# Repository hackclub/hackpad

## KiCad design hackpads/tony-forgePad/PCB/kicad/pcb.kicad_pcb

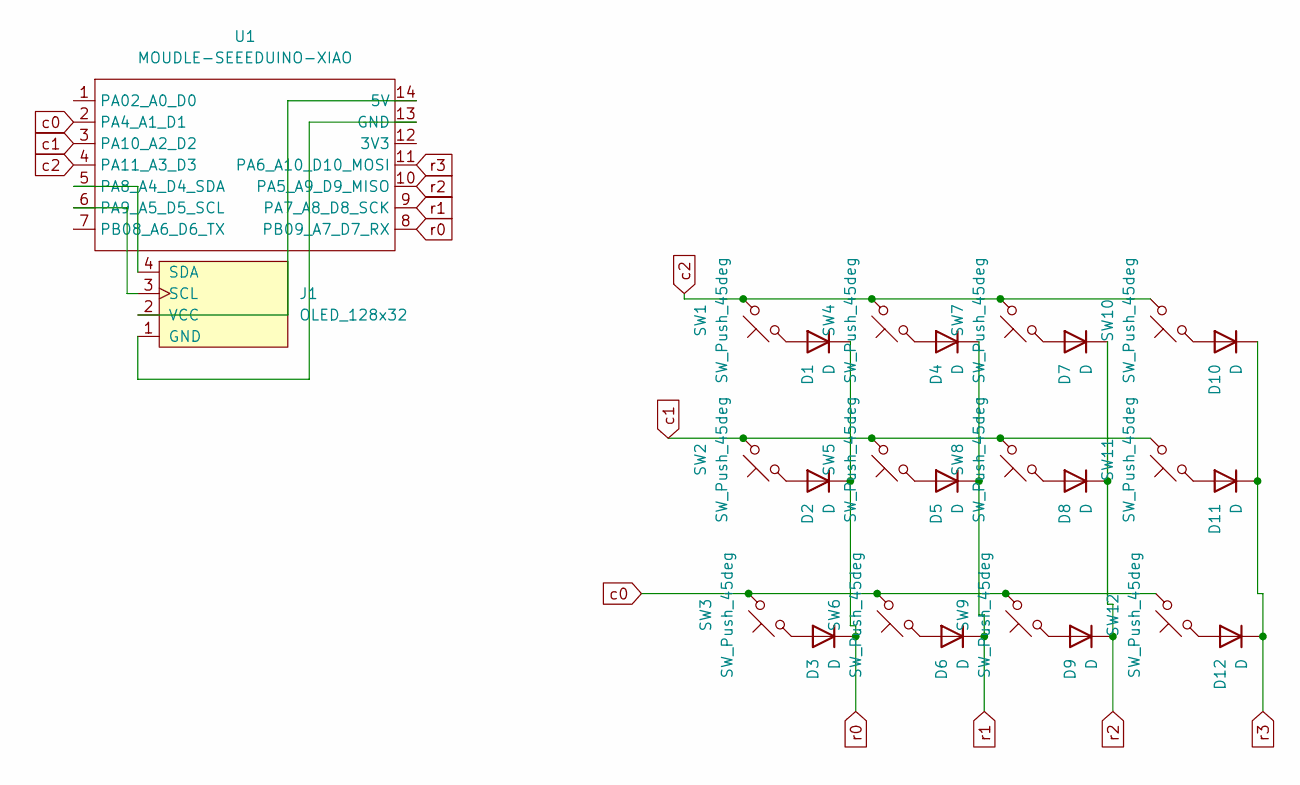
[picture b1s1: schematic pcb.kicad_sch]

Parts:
D1, D2, D3, D4, D5, D6, D7, D8, D9, D10, D11, D12: D; Diode_DO-35
J1: OLED_128x32
SW1, SW2, SW3, SW4, SW5, SW6, SW7, SW8, SW9, SW10, SW11, SW12: SW_Push_45deg; SW_Cherry_MX_1.00u_PCB
U1: MOUDLE-SEEEDUINO-XIAO; XIAO-Generic-Hybrid-14P-2.54-21X17.8MM

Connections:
unnamed: D1.2 (A), SW1.2
unnamed: D2.2 (A), SW2.2
unnamed: D3.2 (A), SW3.2
unnamed: D4.2 (A), SW4.2
unnamed: D5.2 (A), SW5.2
unnamed: D6.2 (A), SW6.2
unnamed: D7.2 (A), SW7.2
unnamed: D8.2 (A), SW8.2
unnamed: D9.2 (A), SW9.2
unnamed: D10.2 (A), SW10.2
unnamed: D11.2 (A), SW11.2
unnamed: D12.2 (A), SW12.2
unnamed: J1.1 (GND), U1.13 (GND)
unnamed: J1.3 (SCL), U1.6 (PA9_A5_D5_SCL)
unnamed: J1.4 (SDA), U1.5 (PA8_A4_D4_SDA)
unnamed: J1.2 (VCC), U1.14 (5V)
c0: SW3.1, SW6.1, SW9.1, SW12.1, U1.2 (PA4_A1_D1)
c1: SW2.1, SW5.1, SW8.1, SW11.1, U1.3 (PA10_A2_D2)
c2: SW1.1, SW4.1, SW7.1, SW10.1, U1.4 (PA11_A3_D3)
r0: D1.1 (K), D2.1 (K), D3.1 (K), U1.8 (PB09_A7_D7_RX)
r1: D4.1 (K), D5.1 (K), D6.1 (K), U1.9 (PA7_A8_D8_SCK)
r2: D7.1 (K), D8.1 (K), D9.1 (K), U1.10 (PA5_A9_D9_MISO)
r3: D10.1 (K), D11.1 (K), D12.1 (K), U1.11 (PA6_A10_D10_MOSI)

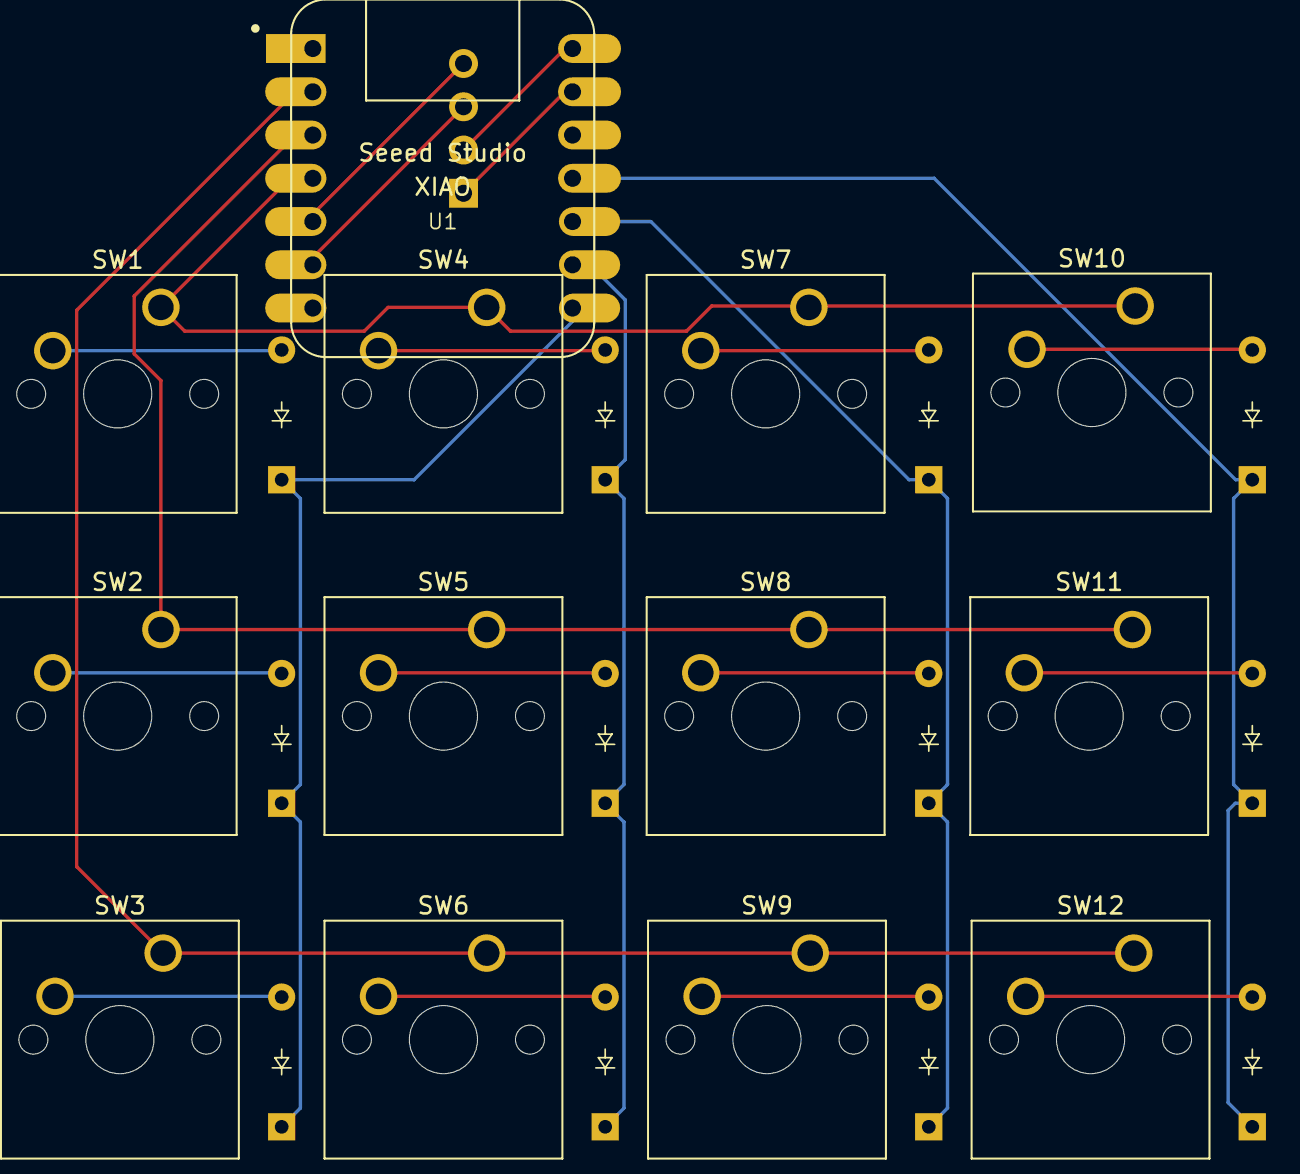
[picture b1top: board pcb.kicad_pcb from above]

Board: 2 copper layers, 26 parts (0 on the bottom side), 23 nets.

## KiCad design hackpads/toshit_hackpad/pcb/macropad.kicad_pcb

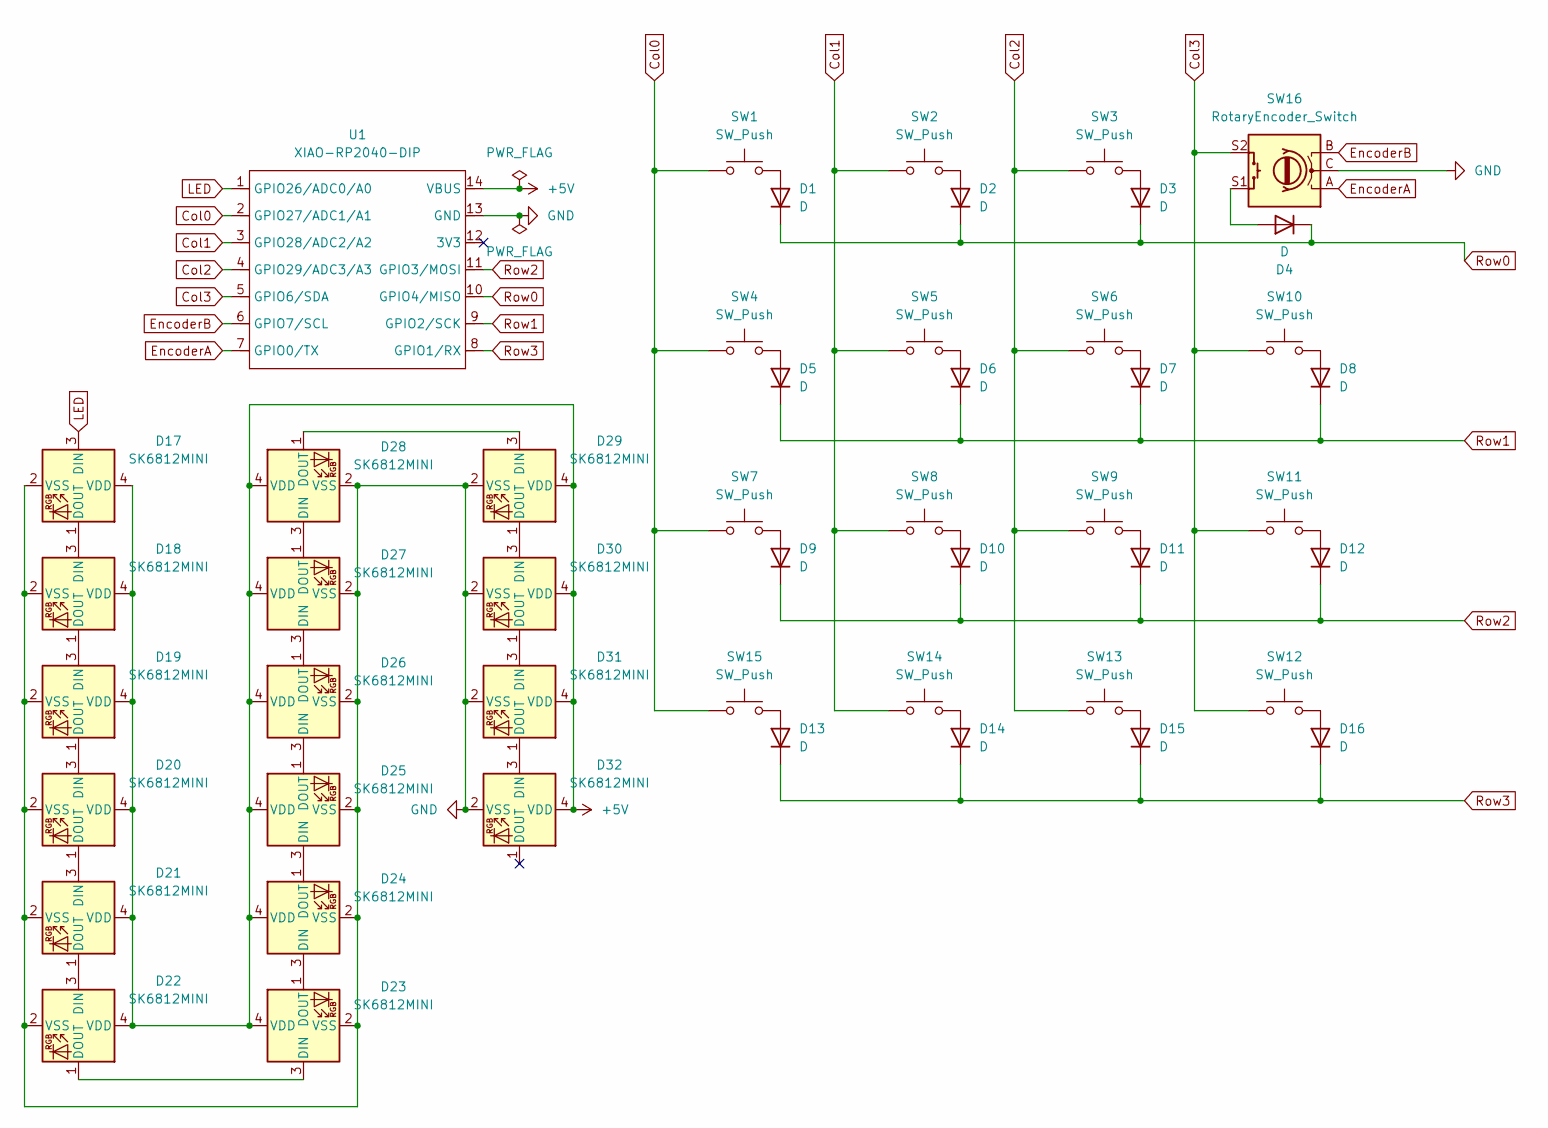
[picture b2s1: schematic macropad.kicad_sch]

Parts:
D1, D2, D3, D4, D5, D6, D7, D8, D9, D10, D11, D12, D13, D14, D15, D16: D; DIODE-1N4148
D17, D18, D19, D20, D21, D22, D23, D24, D25, D26, D27, D28, D29, D30, D31, D32: SK6812MINI; LED_SK6812MINI_PLCC4_3.5x3.5mm_P1.75mm
SW1, SW2, SW3, SW4, SW5, SW6, SW7, SW8, SW9, SW10, SW11, SW12, SW13, SW14, SW15: SW_Push; SW_Cherry_MX_1.00u_PCB
SW16: RotaryEncoder_Switch; RotaryEncoder_Alps_EC11E-Switch_Vertical_H20mm
U1: XIAO-RP2040-DIP

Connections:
+5V: D17.4 (VDD), D18.4 (VDD), D19.4 (VDD), D20.4 (VDD), D21.4 (VDD), D22.4 (VDD), D23.4 (VDD), D24.4 (VDD), D25.4 (VDD), D26.4 (VDD), D27.4 (VDD), D28.4 (VDD), D29.4 (VDD), D30.4 (VDD), D31.4 (VDD), D32.4 (VDD), U1.14 (VBUS)
Col0: SW1.1, SW4.1, SW7.1, SW15.1, U1.2 (GPIO27/ADC1/A1)
Col1: SW2.1, SW5.1, SW8.1, SW14.1, U1.3 (GPIO28/ADC2/A2)
Col2: SW3.1, SW6.1, SW9.1, SW13.1, U1.4 (GPIO29/ADC3/A3)
Col3: SW10.1, SW11.1, SW12.1, SW16.S2, U1.5 (GPIO6/SDA)
EncoderA: SW16.A, U1.7 (GPIO0/TX)
EncoderB: SW16.B, U1.6 (GPIO7/SCL)
GND: D17.2 (VSS), D18.2 (VSS), D19.2 (VSS), D20.2 (VSS), D21.2 (VSS), D22.2 (VSS), D23.2 (VSS), D24.2 (VSS), D25.2 (VSS), D26.2 (VSS), D27.2 (VSS), D28.2 (VSS), D29.2 (VSS), D30.2 (VSS), D31.2 (VSS), D32.2 (VSS), SW16.C, U1.13 (GND)
LED: D17.3 (DIN), U1.1 (GPIO26/ADC0/A0)
unnamed: D1.2 (A), SW1.2
unnamed: D2.2 (A), SW2.2
unnamed: D3.2 (A), SW3.2
unnamed: D4.2 (A), SW16.S1
unnamed: D5.2 (A), SW4.2
unnamed: D6.2 (A), SW5.2
unnamed: D7.2 (A), SW6.2
unnamed: D8.2 (A), SW10.2
unnamed: D9.2 (A), SW7.2
unnamed: D10.2 (A), SW8.2
unnamed: D11.2 (A), SW9.2
unnamed: D12.2 (A), SW11.2
unnamed: D13.2 (A), SW15.2
unnamed: D14.2 (A), SW14.2
unnamed: D15.2 (A), SW13.2
unnamed: D16.2 (A), SW12.2
unnamed: D17.1 (DOUT), D18.3 (DIN)
unnamed: D18.1 (DOUT), D19.3 (DIN)
unnamed: D19.1 (DOUT), D20.3 (DIN)
unnamed: D20.1 (DOUT), D21.3 (DIN)
unnamed: D21.1 (DOUT), D22.3 (DIN)
unnamed: D22.1 (DOUT), D23.3 (DIN)
unnamed: D23.1 (DOUT), D24.3 (DIN)
unnamed: D24.1 (DOUT), D25.3 (DIN)
unnamed: D25.1 (DOUT), D26.3 (DIN)
unnamed: D26.1 (DOUT), D27.3 (DIN)
unnamed: D27.1 (DOUT), D28.3 (DIN)
unnamed: D28.1 (DOUT), D29.3 (DIN)
unnamed: D29.1 (DOUT), D30.3 (DIN)
unnamed: D30.1 (DOUT), D31.3 (DIN)
unnamed: D31.1 (DOUT), D32.3 (DIN)
Row0: D1.1 (K), D2.1 (K), D3.1 (K), D4.1 (K), U1.10 (GPIO4/MISO)
Row1: D5.1 (K), D6.1 (K), D7.1 (K), D8.1 (K), U1.9 (GPIO2/SCK)
Row2: D9.1 (K), D10.1 (K), D11.1 (K), D12.1 (K), U1.11 (GPIO3/MOSI)
Row3: D13.1 (K), D14.1 (K), D15.1 (K), D16.1 (K), U1.8 (GPIO1/RX)

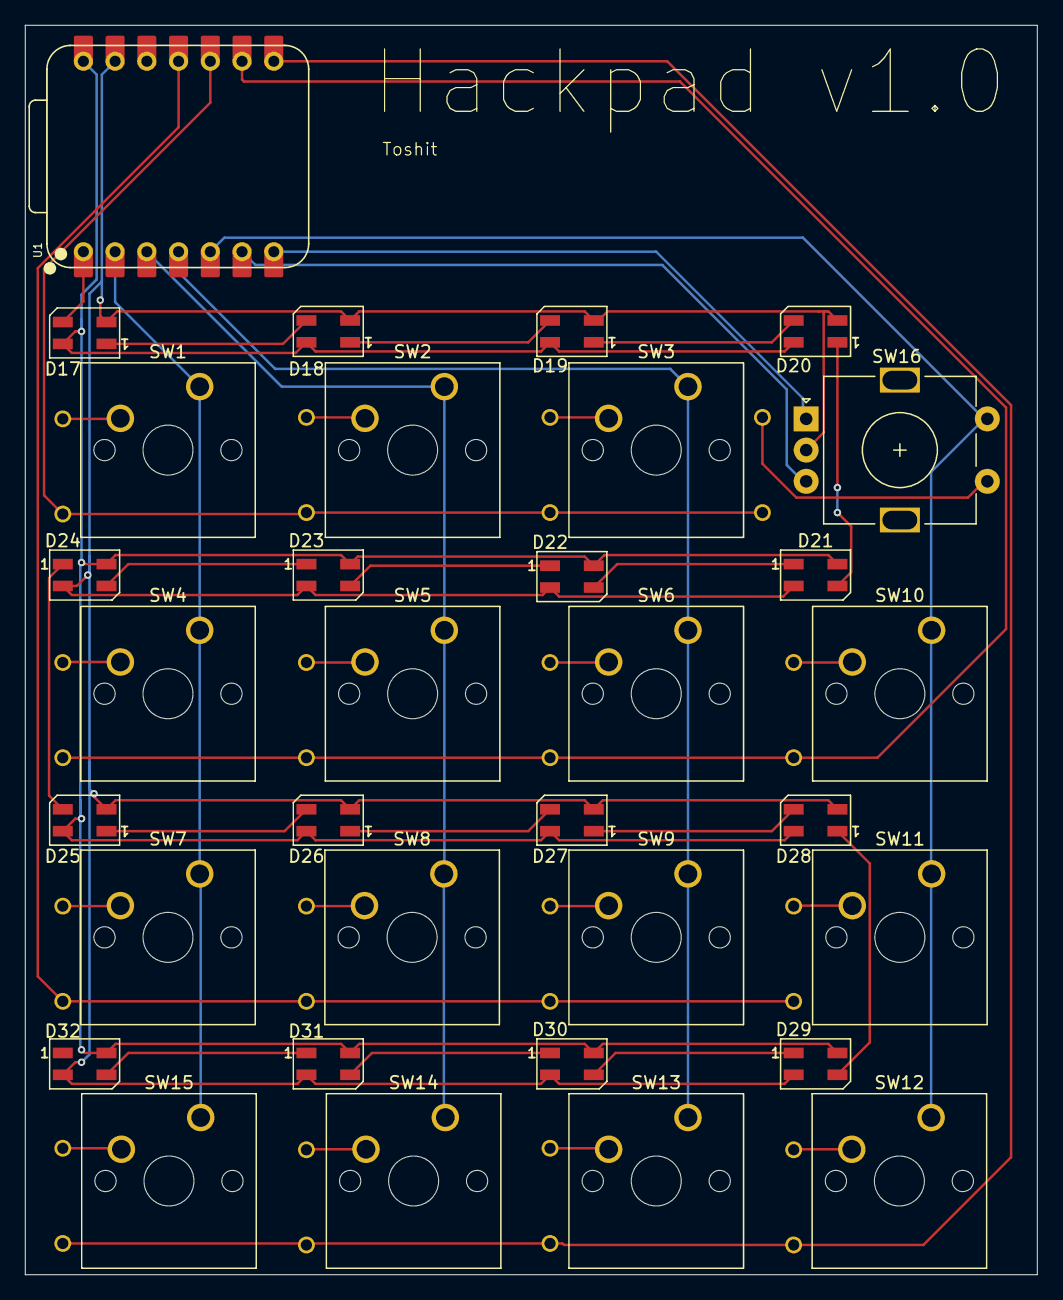
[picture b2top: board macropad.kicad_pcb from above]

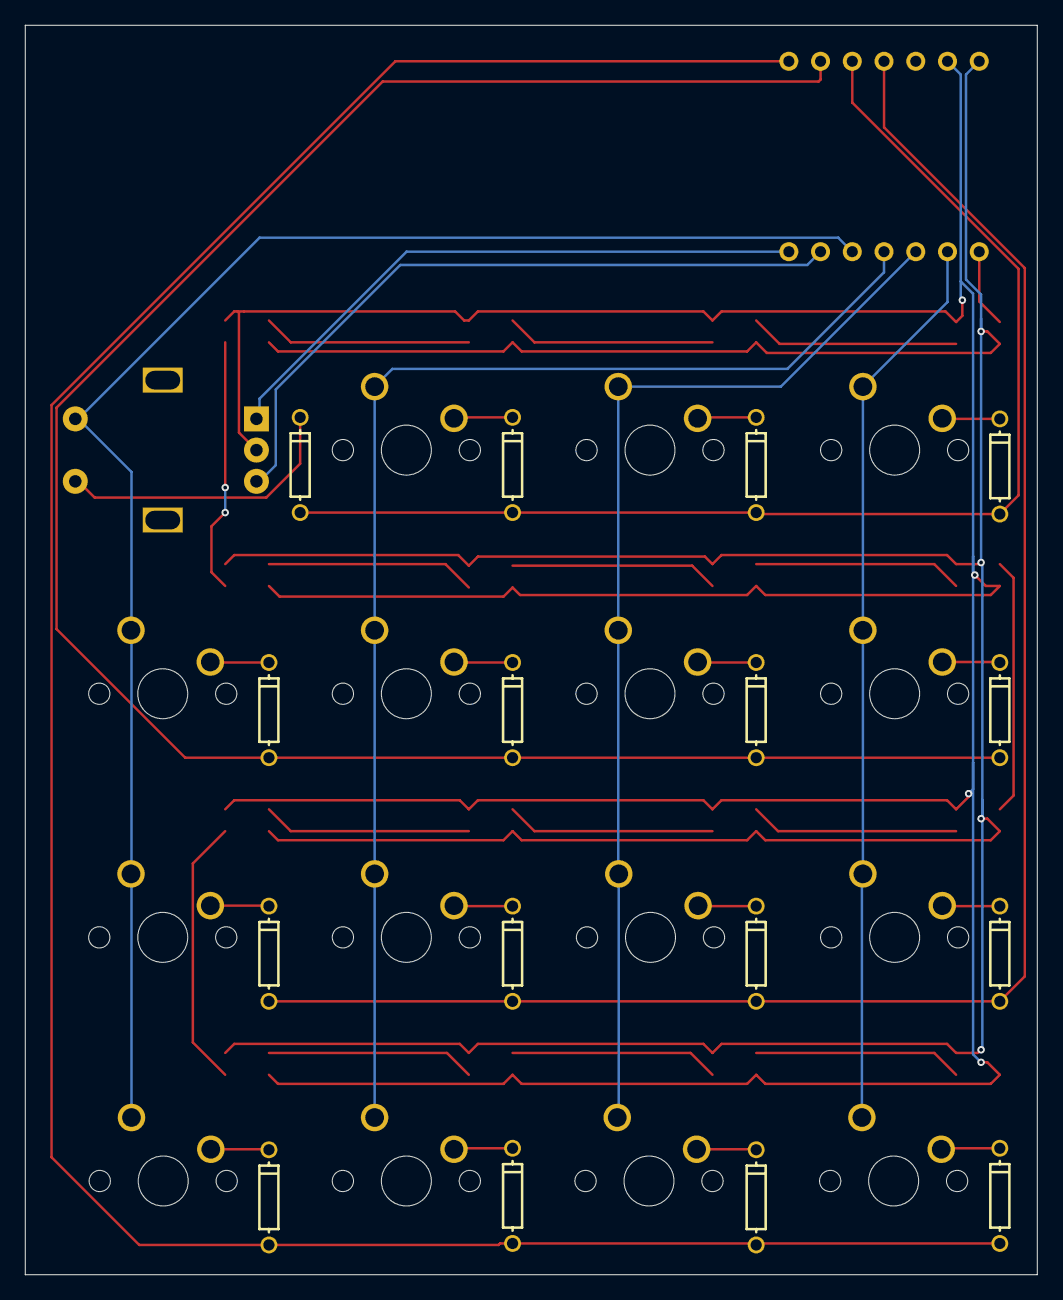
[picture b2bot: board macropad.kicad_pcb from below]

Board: 2 copper layers, 81.0 x 100.0 mm, 49 parts (16 on the bottom side), 44 nets.

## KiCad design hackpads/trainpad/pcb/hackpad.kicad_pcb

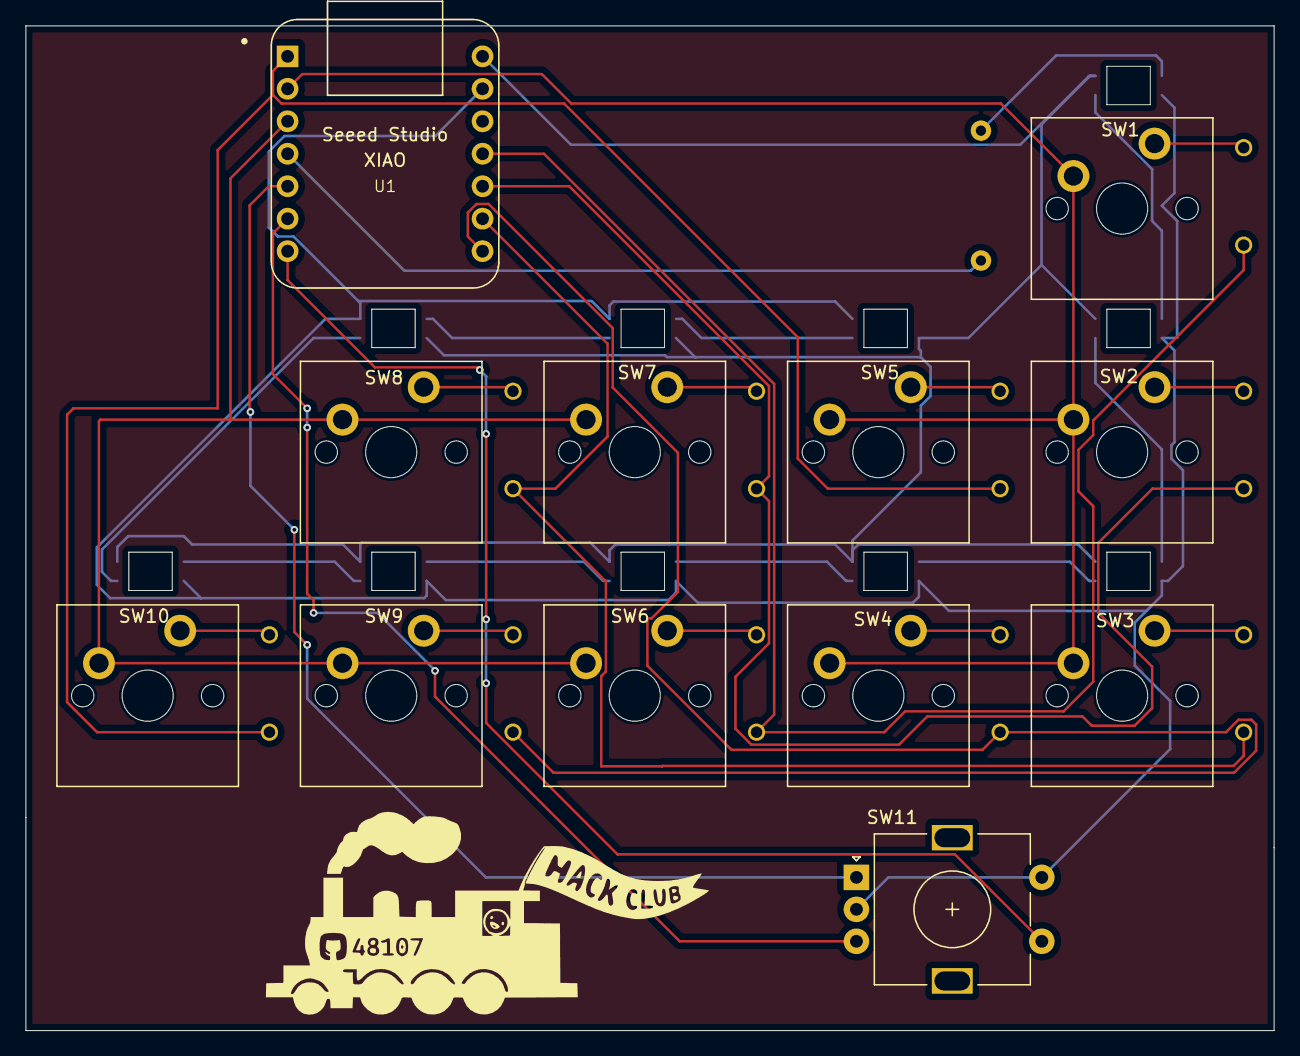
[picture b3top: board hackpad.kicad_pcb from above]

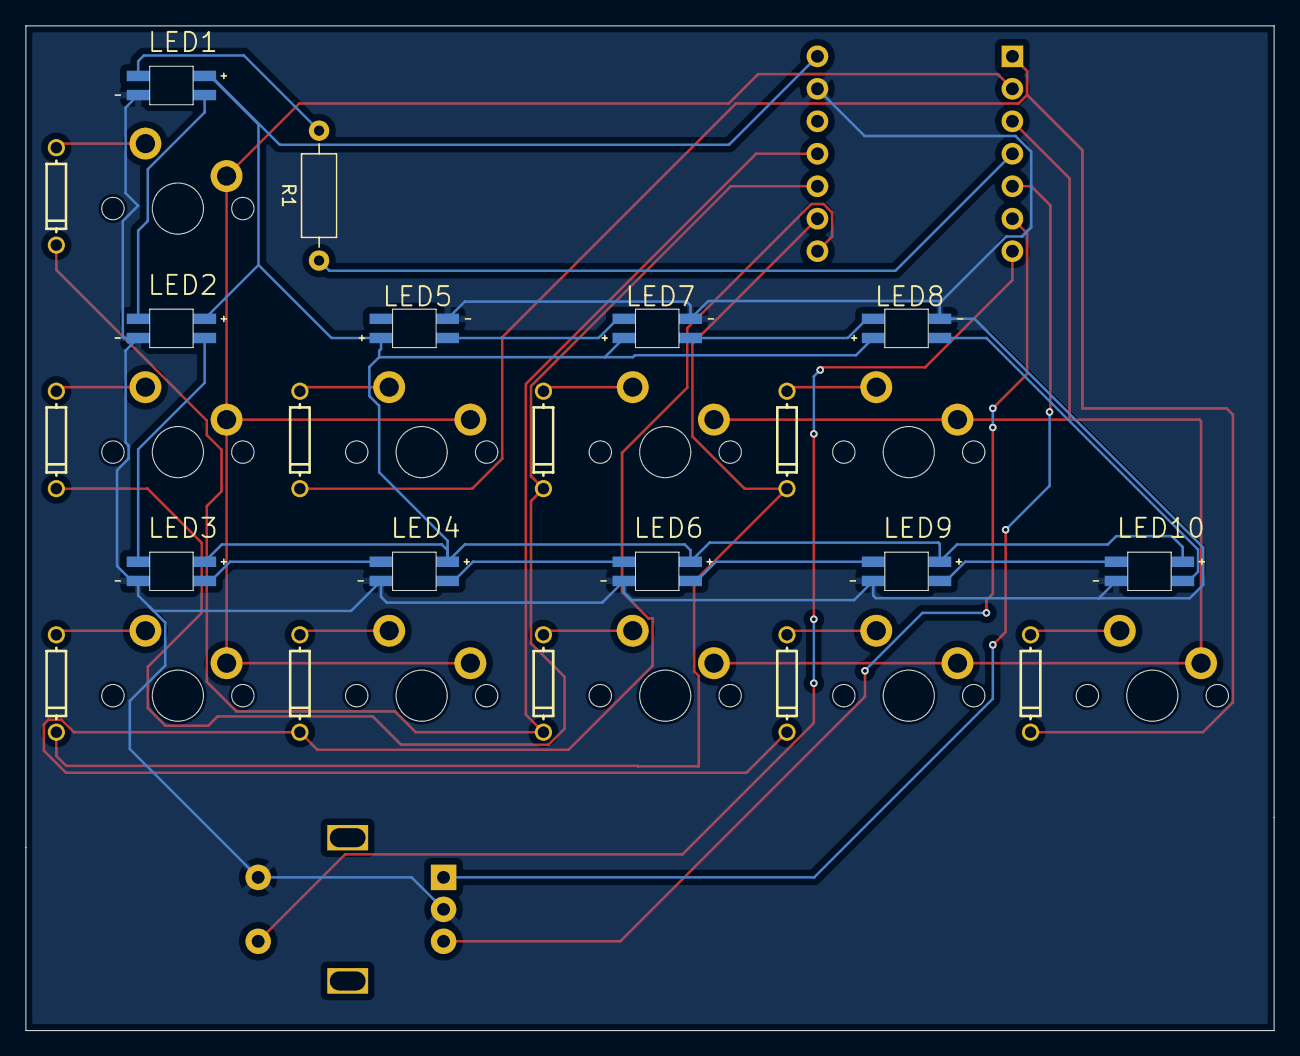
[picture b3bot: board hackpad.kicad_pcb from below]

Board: 2 copper layers, 97.6 x 78.6 mm, 33 parts (21 on the bottom side), 33 nets.

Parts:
D1, D2, D3, D4, D5, D6, D7, D8, D9, D10: DIODE-1N4148
LED1, LED2, LED3, LED4, LED5, LED6, LED7, LED8, LED9, LED10: WS2812B; LED_SK6812-E
R1: 500Ω; R_Axial_DIN0207_L6.3mm_D2.5mm_P10.16mm_Horizontal
SW1, SW2, SW3, SW4, SW5, SW6, SW7, SW8, SW9, SW10: Push_Button; SW_Cherry_MX_PCB_1.00u
SW11: RotaryEncoder_Switch; RotaryEncoder_Alps_EC11E-Switch_Vertical_H20mm
U1: Seeed Studio XIAO SAMD21; XIAO-Generic-Thruhole-14P-2.54-21X17.8MM

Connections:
C0: SW1.1, SW2.1, SW3.1, SW4.1, SW5.1, U1.2 (PA4_A1_D1)
C1: SW6.1, SW7.1, SW8.1, SW9.1, SW10.1, U1.3 (PA10_A2_D2)
D_OUT: LED9.2 (DOUT), LED10.4 (DIN)
LED_IN: R1.1, U1.4 (PA11_A3_D3)
unnamed: D1.A, SW1.2
unnamed: D2.A, SW2.2
unnamed: D3.A, SW3.2
unnamed: D4.A, SW4.2
unnamed: D5.A, SW5.2
unnamed: D6.A, SW6.2
unnamed: D7.A, SW7.2
unnamed: D8.A, SW8.2
unnamed: D9.A, SW9.2
unnamed: D10.A, SW10.2
unnamed: LED1.4 (DIN), R1.2
unnamed: LED1.2 (DOUT), LED2.4 (DIN)
unnamed: LED2.2 (DOUT), LED3.4 (DIN)
unnamed: LED3.2 (DOUT), LED4.4 (DIN)
unnamed: LED4.2 (DOUT), LED6.4 (DIN)
unnamed: LED5.4 (DIN), LED7.2 (DOUT)
unnamed: LED6.2 (DOUT), LED9.4 (DIN)
unnamed: LED7.4 (DIN), LED8.2 (DOUT)
unnamed: LED8.4 (DIN), LED10.2 (DOUT)
P,+5: LED1.1 (VCC), LED2.1 (VCC), LED3.1 (VCC), LED4.1 (VCC), LED5.1 (VCC), LED6.1 (VCC), LED7.1 (VCC), LED8.1 (VCC), LED9.1 (VCC), LED10.1 (VCC), U1.14 (5V)
P,GND: LED1.3 (GND), LED2.3 (GND), LED3.3 (GND), LED4.3 (GND), LED5.3 (GND), LED6.3 (GND), LED7.3 (GND), LED8.3 (GND), LED9.3 (GND), LED10.3 (GND), SW11.C, SW11.S2, U1.13 (GND)
R0: D1.K, D6.K, U1.11 (PA6_A10_D10_MOSI)
R1: D2.K, D7.K, U1.10 (PA5_A9_D9_MISO)
R2: D3.K, D8.K, U1.9 (PA7_A8_D8_SCK)
R3: D4.K, D9.K, U1.8 (PB09_A7_D7_RX)
R4: D5.K, D10.K, U1.1 (PA02_A0_D0)
REA: SW11.A, U1.5 (PA8_A4_D4_SDA)
REB: SW11.B, U1.6 (PA9_A5_D5_SCL)
RES: SW11.S1, U1.7 (PB08_A6_D6_TX)

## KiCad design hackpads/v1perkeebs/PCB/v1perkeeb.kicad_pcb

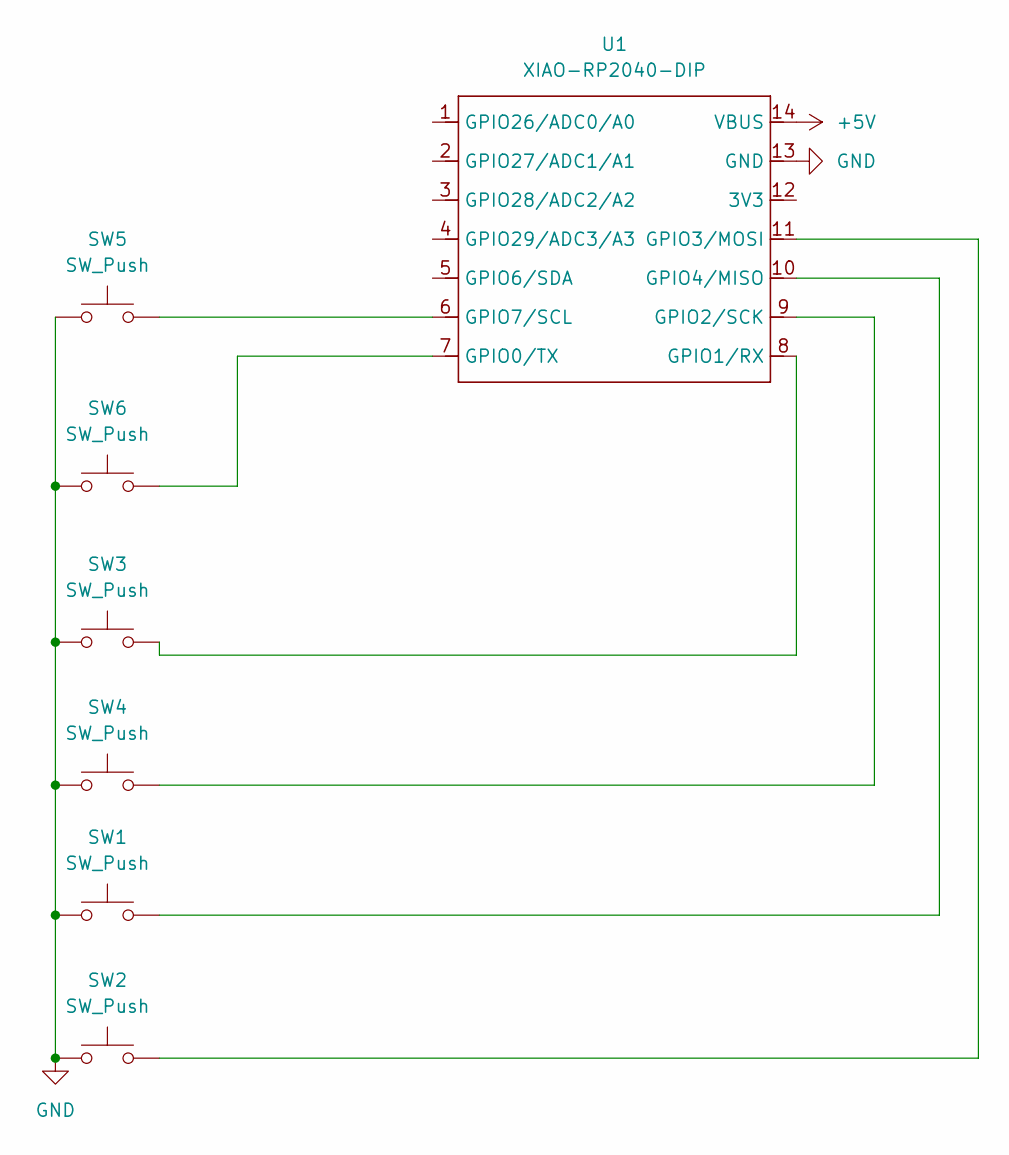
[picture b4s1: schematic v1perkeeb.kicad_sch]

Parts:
SW1, SW2, SW3, SW4, SW5, SW6: SW_Push; SW_Cherry_MX_1.00u_PCB
U1: XIAO-RP2040-DIP

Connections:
+5V: U1.14 (VBUS)
GND: SW1.1, SW2.1, SW3.1, SW4.1, SW5.1, SW6.1, U1.13 (GND)
unnamed: SW6.2, U1.7 (GPIO0/TX)
unnamed: SW3.2, U1.8 (GPIO1/RX)
unnamed: SW4.2, U1.9 (GPIO2/SCK)
unnamed: SW2.2, U1.11 (GPIO3/MOSI)
unnamed: SW1.2, U1.10 (GPIO4/MISO)
unnamed: SW5.2, U1.6 (GPIO7/SCL)

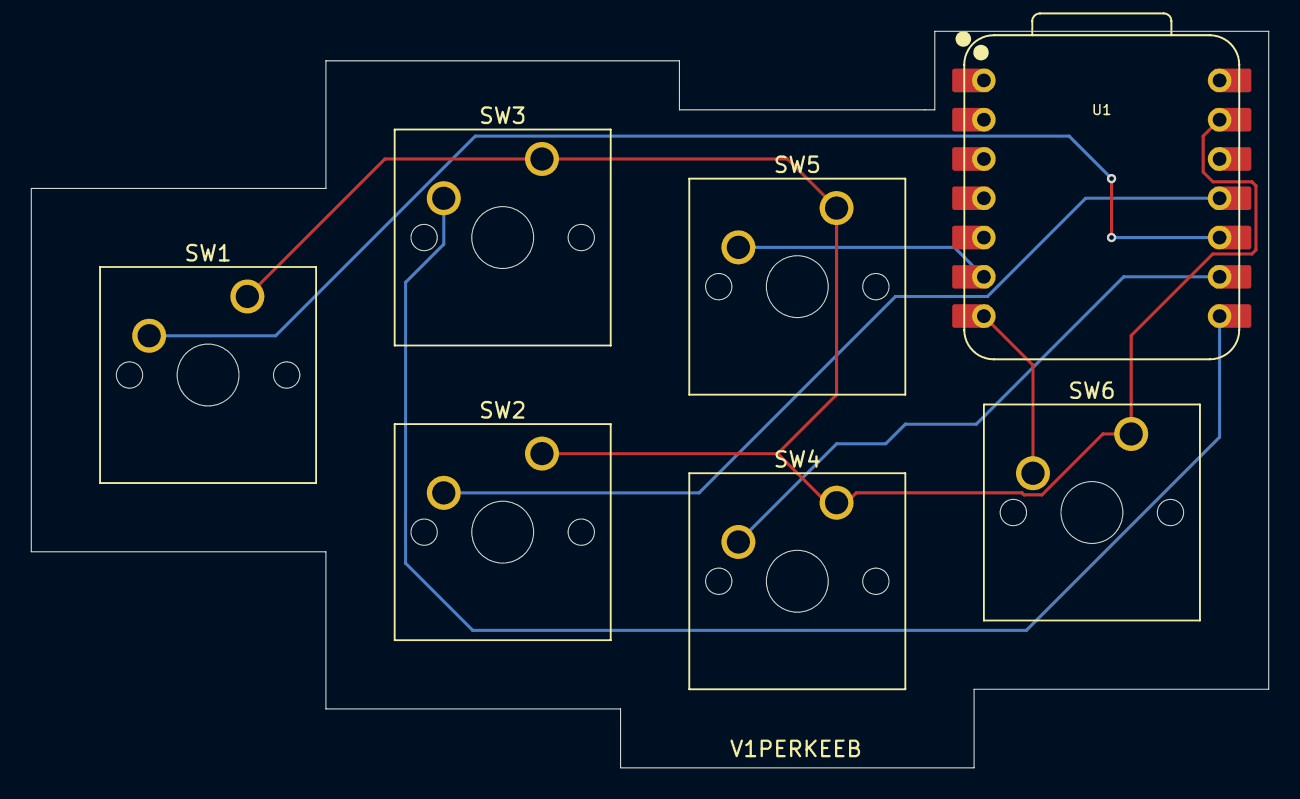
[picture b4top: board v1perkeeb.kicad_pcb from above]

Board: 2 copper layers, 80.0 x 47.6 mm, 7 parts (0 on the bottom side), 7 nets.
